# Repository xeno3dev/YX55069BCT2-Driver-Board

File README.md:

# LumaDD

## Overview

LumaDD is a Custom Display Driver Board designed around a display I got off [Alibaba](https://www.alibaba.com/product-detail/5-5-Vertical-Smart-Home-lcd_1601790231031.html?spm=a2756.trade-list-buyer.0.0.36a276e9iccSGK), with Touch Support. It features HDMI -> MIPI DSI video signal conversion, USB-C for Touch Signals + Power, as well as an onboard ESP32-S3 for display control + touch processing (via USB HID)

## Repo Directory

Folder | Contents
|---|---|
Component Libs | All 3D Models. Footprints, and Symbols used on the PCB
Kicad Project | Schematic + PCB Files
Production Files | BOM + CPL + Netlist + Designator + Gerber Files

## Rough BOM
| Part / Group | What’s included | Qty | Cost (USD) |
| --- | --- | ---: | ---: |
| Converter BGA | [TC358870XBG](https://www.lcsc.com/product-detail/C3008712.html), U1 | 1 | $8.86 |
| ESP32 by itself | [ESP32-S3R8](https://www.lcsc.com/product-detail/C2913194.html), U10 | 1 | $3.02 |
| Flash memory | [GD25Q128EWIGR](https://www.lcsc.com/product-detail/C2982923.html), U11 | 1 | $3.33 |
| HDMI port | [Amphenol 10029449-111RLF](https://www.lcsc.com/product-detail/C427307.html) | 1 | $0.62 |
| USB-C port | [TYPE-C16PIN](https://www.lcsc.com/product-detail/C393939.html) | 1 | $0.06 |
| Display connector | [24-pin FPC](https://www.lcsc.com/product-detail/C132514.html) | 1 | $0.25 |
| Touch connector | [6-pin FPC](https://www.lcsc.com/product-detail/C5343255.html) | 1 | $0.15 |
| Power regulation and input control | Five TLV767 regulators, CH224K, TPS259474 eFuse | 7 | $3.64 |
| Backlight power stage | TPS61165, inductor, diode | 3 | $1.09 |
| Logic level shifters | Two PCA9306, TXS0101, SN74AXC1T45 | 4 | $2.39 |
| ESD / surge protection | D3–D5, U8, U12, U16 | 6 | $1.46 |
| Clock components | 40 MHz crystal and 48 MHz oscillator | 2 | $1.50 |
| Boot / reset buttons | SW3 and SW4 | 2 | $2.29 |
| Capacitors | All BOM capacitors | 72 | $1.97 |
| Resistors | All BOM resistors | 40 | $0.36 |
| MOSFETs | Three BSS138 | 3 | $0.06 |
| Ferrite beads | FB1 and FB2 | 2 | $0.03 |
| **Total parts used** | **148 components** | **148** | **$31.07** |

### Full BOM Located [Here](./Production%20Files/bom.csv)

## License

[Attribution-NonCommercial-ShareAlike 4.0 International](./LICENSE)

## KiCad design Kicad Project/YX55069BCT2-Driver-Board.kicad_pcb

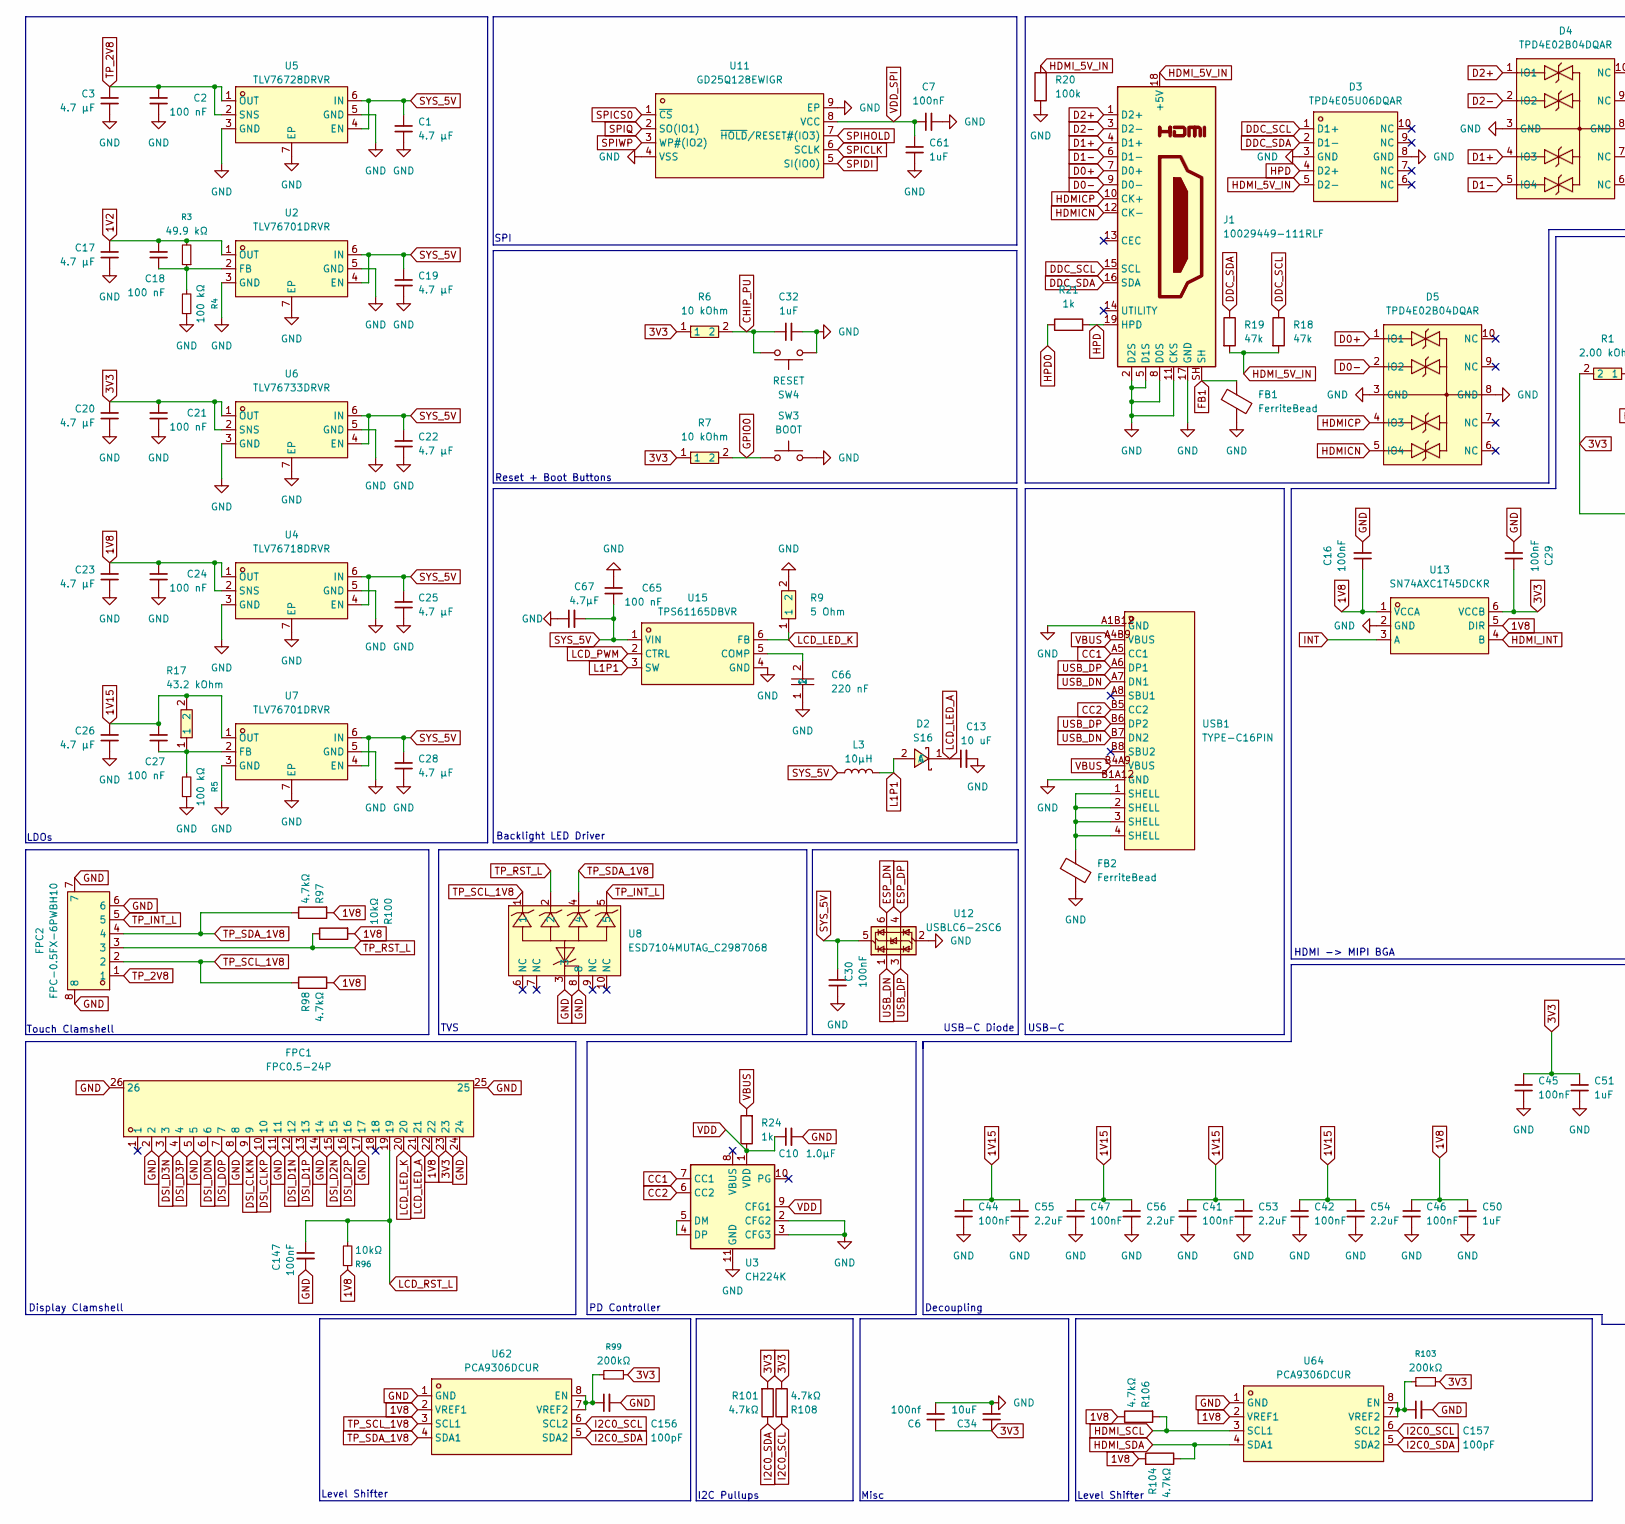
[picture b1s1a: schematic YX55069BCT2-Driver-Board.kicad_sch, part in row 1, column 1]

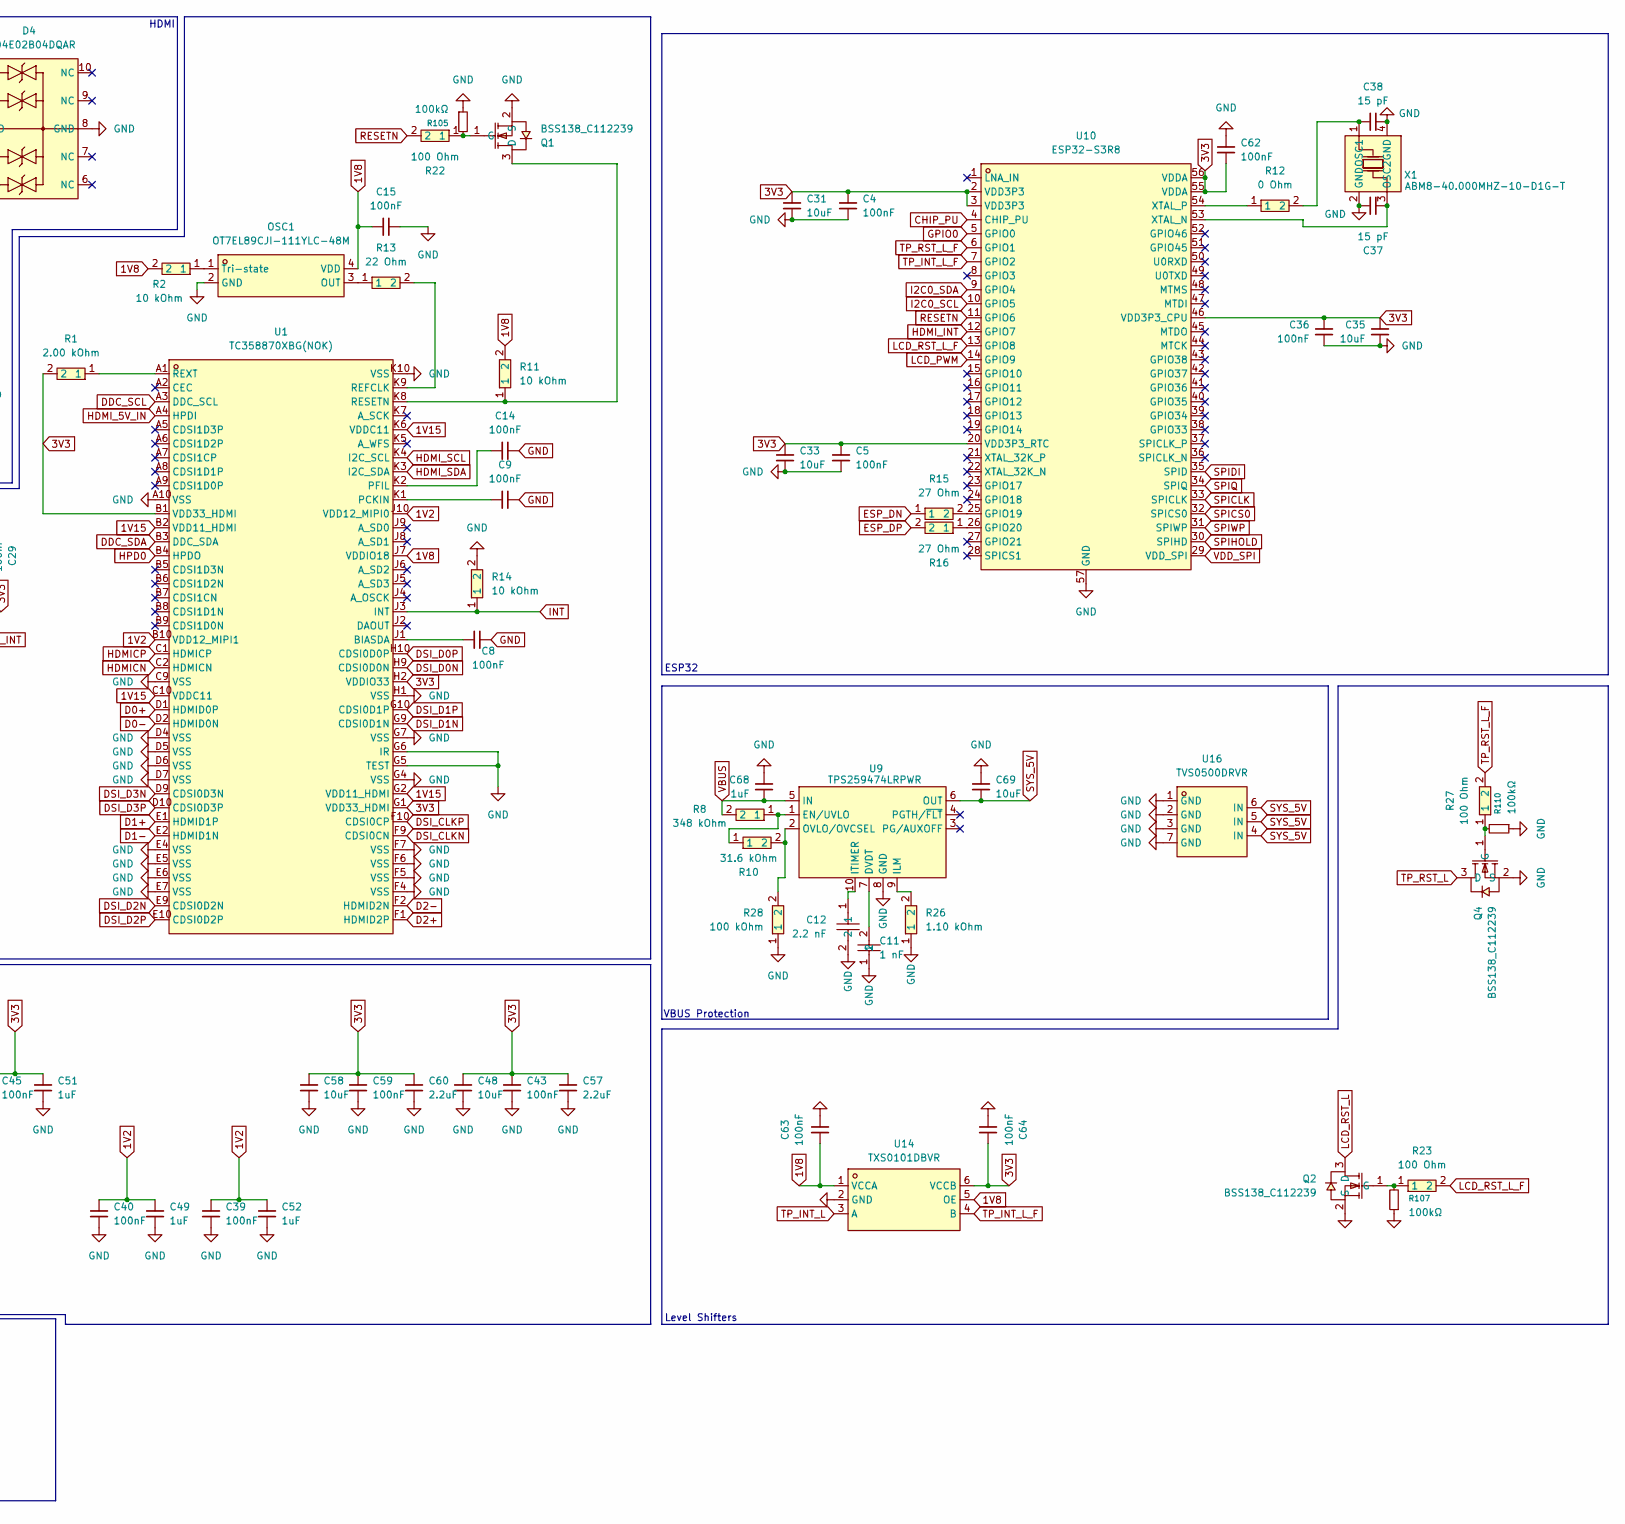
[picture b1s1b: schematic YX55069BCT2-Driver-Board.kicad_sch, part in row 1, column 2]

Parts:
C1, C3, C17, C19, C20, C22, C23, C25, C26, C28: 4.7 µF; C_0603_1608Metric; LCSC C69335
C2, C18, C21, C24, C27, C65: 100 nF; C_0603_1608Metric; LCSC C1591
C4, C5, C7, C8, C9, C14, C15, C16, C29, C30, C36, C39, C40, C41, C42, C43, C44, C45, C46, C47, C59, C62, C63, C64: 100nF; C0603; LCSC C1591
C6: 100nf; C0603; LCSC C1591
C10: 1.0µF; C_0603_1608Metric; MPN CL10A105KA8NNNC; LCSC Part C5673
C11: 1 nF; C0402; Tolerance 10%; Voltage 50 V; MPN CL05B102KB5NNNC; LCSC C14442
C12: 2.2 nF; C0402; Tolerance 10%; Voltage 50 V; MPN CL05B222KB5NNNC; LCSC C84703
C13: 10 uF; C1206; LCSC Part C100122
C31, C33, C34, C35, C48, C58, C69: 10uF; C0603; LCSC C77044
C32, C68: 1uF; CL05A105KA5NQNC; LCSC C52923
C37, C38: 15 pF; C0402; LCSC C86285
C49, C50, C51, C52, C61: 1uF; C0603; LCSC C29936
C53, C54, C55, C56, C57, C60: 2.2uF; C0603; LCSC C23630
C66: 220 nF; C0402; Tolerance 10%; Voltage 16 V; MPN CL05B224KO5NNNC; LCSC C16772
C67: 4.7µF; C0805; LCSC Part C2897302
C147: 100nF; C_0603_1608Metric; MPN CL10B104KB8NNNC; LCSC Part C1591
C156, C157: 100pF; C_0603_1608Metric; MPN CL10C101JB8NNNC; LCSC Part C14858
D2: S16; SOD-123FL_L2.7-W1.8-LS3.8-RD; MPN S16; LCSC C405304
D3: TPD4E05U06DQAR; USON-10_L2.5-W1.0-P0.50-BL; MPN TPD4E05U06DQAR; LCSC C138714
D4, D5: TPD4E02B04DQAR; USON-10_L2.5-W1.0-P0.50-BL; MPN TPD4E02B04DQAR; LCSC C106794
FB1, FB2: FerriteBead; L_0603_1608Metric; LCSC C14709
FPC1: FPC0.5-24P; FPC-SMD_P0.50-24P_XJ-FGS; MPN F-FPC0M24P-C310; LCSC Part C132514
FPC2: FPC-0.5FX-6PWBH10; FPC-SMD_FPC-0.5FX-6PWBH10; MPN FPC-0.5FX-6PWBH10; LCSC Part C5343255
J1: 10029449-111RLF; HDMI_A_Amphenol_10029449-x01xLF_Horizontal; MPN 10029449-001RLF; LCSC C427307
L3: 10µH; IND-SMD_L7.1-W6.6; MPN SPM6530T-100M; LCSC Part C112288
OSC1: OT7EL89CJI-111YLC-48M; OSC-SMD_4P-L2.0-W1.6-BL; Supply Voltage 1.8–3.3 V; MPN OT7EL89CJI-111YLC-48M; LCSC C7434946
Q1, Q2, Q4: BSS138_C112239; SOT-23-3_L2.9-W1.6-P1.90-LS2.8-BR; MPN BSS138; LCSC C112239
R1: 2.00 kOhm; R0402; Tolerance 1%; MPN RC0402FR-072KL; LCSC C60488
R2, R6, R7, R11, R14: 10 kOhm; R0402; Tolerance 1%; MPN RC0402FR-0710KL; LCSC C60490
R3: 49.9 kΩ; R_0805_2012Metric; LCSC C17719
R4, R5: 100 kΩ; R_0805_2012Metric; LCSC C149504
R8: 348 kOhm; R0402; Voltage 50 V; Tolerance 1%; MPN 0402WGF3483TCE; LCSC C25780
R9: 5 Ohm; R0402; Voltage 50 V; Tolerance 1%; MPN CSRT0402FT5R00; LCSC C6888654
R10: 31.6 kOhm; R0402; Voltage 50 V; Tolerance 1%; MPN 0402WGF3162TCE; LCSC C11463
R12: 0 Ohm; R0402; Tolerance 1%; MPN RC0402FR-070RL; LCSC C106231
R13: 22 Ohm; R0402; Tolerance 1%; MPN RC0402FR-0722RL; LCSC C114765
R15, R16: 27 Ohm; R0402; Tolerance 1%; MPN RC0402FR-0727RL; LCSC C138021
R17: 43.2 kOhm; R0402; Voltage 50 V; Tolerance 1%; MPN 0402WGF4322TCE; LCSC C25894
R18, R19: 47k; R_0603_1608Metric; LCSC C2907042
R20: 100k; R_0603_1608Metric; LCSC C14675
R21, R24: 1k; R_0603_1608Metric; LCSC C22548
R22, R23, R27: 100 Ohm; R0402; Tolerance 1%; MPN RC0402FR-07100RL; LCSC C106232
R26: 1.10 kOhm; R0402; Voltage 50 V; Tolerance 1%; MPN 0402WGF1101TCE; LCSC C25860
R28: 100 kOhm; R0402; Voltage 50 V; Tolerance 1%; MPN 0402WGF1003TCE; LCSC C25741
R96, R100: 10kΩ; R_0603_1608Metric; MPN CR0603-FX-1002ELF; LCSC Part C840630
R97, R98, R101, R104, R106, R108: 4.7kΩ; R_0603_1608Metric; MPN WR06X4701FTL; LCSC Part C163914
R99, R103: 200kΩ; R_0603_1608Metric; MPN ERJ3EKF2003V; LCSC Part C118142
R105, R107, R110: 100kΩ; R_0603_1608Metric; MPN 0603WAF1003T5E; LCSC Part C25803
SW3: BOOT; KEY-SMD_KMR2XXGXXX; MPN KMR231GLFS; LCSC Part C99271
SW4: RESET; KEY-SMD_KMR2XXGXXX; MPN KMR231GLFS; LCSC Part C99271
U1: TC358870XBG(NOK); P-VFBGA-80_L7.0-W7.0-R10-C10-P0.65-TL; MPN TC358870XBG(NOK); LCSC C3008712
U2, U7: TLV76701DRVR; WSON-6_L2.0-W2.0-P0.65-TL-EP; Output Voltage 1.0 V; MPN TLV76701DRVR; LCSC C2863998
U3: CH224K; SSOP-10-1EP_3.9x4.9mm_P1mm_EP2.1x3.3mm; MPN CH224K; LCSC Part C970725
U4: TLV76718DRVR; WSON-6_L2.0-W2.0-P0.65-BL-EP; Output Voltage 1.8 V; MPN TLV76718DRVR; LCSC C2870458
U5: TLV76728DRVR; WSON-6_L2.0-W2.0-P0.65-BL-EP; Output Voltage 2.8 V; MPN TLV76728DRVR; LCSC C2865665
U6: TLV76733DRVR; WSON-6_L2.0-W2.0-P0.65-TL-EP; Output Voltage 3.3 V; MPN TLV76733DRVR; LCSC C2848334
U8: ESD7104MUTAG_C2987068; DFN-10_L2.5-W1.0-P0.50-BL; MPN ESD7104MUTAG; LCSC Part C2987068
U9: TPS259474LRPWR; VQFN-10_L2.0-W2.0-P0.45-TL; MPN TPS259474LRPWR; LCSC C2864845
U10: ESP32-S3R8; QFN-56_L7.0-W7.0-P0.40-TL-EP4.0; MPN ESP32-S3R8; LCSC C2913194
U11: GD25Q128EWIGR; WSON-8_L6.0-W5.0-P1.27-TL-EP; MPN GD25Q128EWIGR; LCSC C2982923
U12: USBLC6-2SC6; SOT-23-6; LCSC C7519
U13: SN74AXC1T45DCKR; SC-70-6_L2.0-W1.3-P0.65-LS2.1-BL-1; MPN SN74AXC1T45DCKR; LCSC Part C2677392
U14: TXS0101DBVR; SOT-23-6_L2.9-W1.6-P0.95-LS2.8-BR; MPN TXS0101DBVR; LCSC C132604
U15: TPS61165DBVR; SOT-23-6_L2.9-W1.6-P0.95-LS2.8-BR; MPN TPS61165DBVR; LCSC C58756
U16: TVS0500DRVR; WSON-6_L2.0-W2.0-P0.65-BL-EP; MPN TVS0500DRVR; LCSC C609571
U62, U64: PCA9306DCUR; SSOP-8_L2.0-W2.3-P0.50-LS3.1-BR; MPN PCA9306DCUR; LCSC Part C33196
USB1: TYPE-C16PIN; USB-C-SMD_TYPE-C16PIN; MPN TYPE-C16PIN; LCSC C393939
X1: ABM8-40.000MHZ-10-D1G-T; CRYSTAL-SMD_4P-L3.2-W2.5-BL; MPN ABM8-40.000MHZ-10-D1G-T; LCSC C1986736

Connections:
1V2: C17.2, C18.2, C39.2, C40.2, C49.2, C52.2, R3.2, U1.B10 (VDD12_MIPI1), U1.J10 (VDD12_MIPI0), U2.1 (OUT)
1V8: C15.2, C16.2, C23.2, C24.2, C46.2, C50.2, C63.2, FPC1.22, OSC1.4 (VDD), R2.2, R11.2, R96.1, R97.2, R98.1, R100.2, R104.2, R106.1, U1.J7 (VDDIO18), U4.1 (OUT), U4.2 (SNS), U13.1 (VCCA), U13.5 (DIR), U14.1 (VCCA), U14.5 (OE), U62.2 (VREF1), U64.2 (VREF1)
1V15: C26.2, C27.2, C41.2, C42.2, C44.2, C47.2, C53.2, C54.2, C55.2, C56.2, R17.2, U1.B2 (VDD11_HDMI), U1.C10 (VDDC11), U1.G2 (VDD11_HDMI), U1.K6 (VDDC11), U7.1 (OUT)
3V3: C4.2, C5.2, C6.2, C20.2, C21.2, C29.2, C31.2, C33.2, C34.2, C35.2, C36.2, C43.2, C45.2, C48.2, C51.2, C57.2, C58.2, C59.2, C60.2, C62.2, C64.2, FPC1.23, R1.2, R6.1, R7.1, R99.2, R101.2, R103.2, R108.1, U1.B1 (VDD33_HDMI), U1.G1 (VDD33_HDMI), U1.H2 (VDDIO33), U6.1 (OUT), U6.2 (SNS), U10.2 (VDD3P3), U10.3 (VDD3P3), U10.20 (VDD3P3_RTC), U10.46 (VDD3P3_CPU), U10.55 (VDDA), U10.56 (VDDA), U13.6 (VCCB), U14.6 (VCCB)
CC1: U3.7 (CC1), USB1.A5 (CC1)
CC2: U3.6 (CC2), USB1.B5 (CC2)
CHIP_PU: C32.2, R6.2, SW4.1, U10.4 (CHIP_PU)
D0+: D5.1 (IO1), J1.7 (D0+), U1.D1 (HDMID0P)
D0-: D5.2 (IO2), J1.9 (D0-), U1.D2 (HDMID0N)
D1+: D4.4 (IO3), J1.4 (D1+), U1.E1 (HDMID1P)
D1-: D4.5 (IO4), J1.6 (D1-), U1.E2 (HDMID1N)
D2+: D4.1 (IO1), J1.1 (D2+), U1.F1 (HDMID2P)
D2-: D4.2 (IO2), J1.3 (D2-), U1.F2 (HDMID2N)
DDC_SCL: D3.1 (D1+), J1.15 (SCL), R18.1, U1.A3 (DDC_SCL)
DDC_SDA: D3.2 (D1-), J1.16 (SDA), R19.1, U1.B3 (DDC_SDA)
DSI_CLKN: FPC1.9, U1.F9 (CDSI0CN)
DSI_CLKP: FPC1.10, U1.F10 (CDSI0CP)
DSI_D0N: FPC1.6, U1.H9 (CDSI0D0N)
DSI_D0P: FPC1.7, U1.H10 (CDSI0D0P)
DSI_D1N: FPC1.12, U1.G9 (CDSI0D1N)
DSI_D1P: FPC1.13, U1.G10 (CDSI0D1P)
DSI_D2N: FPC1.15, U1.E9 (CDSI0D2N)
DSI_D2P: FPC1.16, U1.E10 (CDSI0D2P)
DSI_D3N: FPC1.3, U1.D9 (CDSI0D3N)
DSI_D3P: FPC1.4, U1.D10 (CDSI0D3P)
ESP_DN: R15.1, U12.6 (I/O1)
ESP_DP: R16.2, U12.4 (I/O2)
FB1: FB1.1, J1.SH
GND: C1.2, C2.1, C3.1, C4.1, C5.1, C6.1, C7.1, C8.1, C9.1, C10.2, C11.1, C12.2, C13.2, C14.1, C15.1, C16.1, C17.1, C19.2, C20.1, C21.1, C22.2, C23.1, C24.1, C25.2, C26.1, C28.2, C29.1, C30.2, C31.1, C32.1, C33.1, C34.1, C35.1, C36.1, C37.1, C38.1, C39.1, C40.1, C41.1, C42.1, C43.1, C44.1, C45.1, C46.1, C47.1, C48.1, C49.1, C50.1, C51.1, C52.1, C53.1, C54.1, C55.1, C56.1, C57.1, C58.1, C59.1, C60.1, C61.1, C62.1, C63.1, C64.1, C65.2, C66.1, C67.1, C68.1, C69.2, C147.2, C156.2, C157.2, D3.3 (GND), D3.8 (GND), D4.3 (GND), D4.8 (GND), D5.3 (GND), D5.8 (GND), FB1.2, FB2.2, FPC1.2, FPC1.5, FPC1.8, FPC1.11, FPC1.14, FPC1.17, FPC1.24, FPC1.25, FPC1.26, FPC2.6, FPC2.7, FPC2.8, J1.2 (D2S), J1.5 (D1S), J1.8 (D0S), J1.11 (CKS), J1.17 (GND), OSC1.2 (GND), Q1.2 (S), Q2.2 (S), Q4.2 (S), R4.1, R5.1, R9.2, R14.2, R20.2, R26.1, R28.1, R105.1, R107.1, R110.1, SW3.2, SW4.2, U1.A10 (VSS), U1.C9 (VSS), U1.D4 (VSS), U1.D5 (VSS), U1.D6 (VSS), U1.D7 (VSS), U1.E4 (VSS), U1.E5 (VSS), U1.E6 (VSS), U1.E7 (VSS), U1.F4 (VSS), U1.F5 (VSS), U1.F6 (VSS), U1.F7 (VSS), U1.G4 (VSS), U1.G5 (TEST), U1.G6 (IR), U1.G7 (VSS), U1.H1 (VSS), U1.K10 (VSS), U2.3 (GND), U2.5 (GND), U2.7 (EP), U3.2 (CFG2), U3.3 (CFG3), U3.11 (GND), U4.3 (GND), U4.5 (GND), U4.7 (EP), U5.3 (GND), U5.5 (GND), U5.7 (EP), U6.3 (GND), U6.5 (GND), U6.7 (EP), U7.3 (GND), U7.5 (GND), U7.7 (EP), U8.3, U8.8, U9.8 (GND), U10.57 (GND), U11.4 (VSS), U11.9 (EP), U12.2 (GND), U13.2 (GND), U14.2 (GND), U15.4 (GND), U16.1 (GND), U16.2 (GND), U16.3 (GND), U16.7 (GND), U62.1 (GND), U64.1 (GND), USB1.A1B12 (GND), USB1.B1A12 (GND), X1.2 (GND), X1.4 (GND)
GPIO0: R7.2, SW3.1, U10.5 (GPIO0)
HDMICN: D5.5 (IO4), J1.12 (CK-), U1.C2 (HDMICN)
HDMICP: D5.4 (IO3), J1.10 (CK+), U1.C1 (HDMICP)
HDMI_5V_IN: D3.5 (D2-), J1.18 (+5V), R18.2, R19.2, R20.1, U1.A4 (HPDI)
HDMI_INT: U10.12 (GPIO7), U13.4 (B)
HDMI_SCL: R106.2, U1.K4 (I2C_SCL), U64.3 (SCL1)
HDMI_SDA: R104.1, U1.K3 (I2C_SDA), U64.4 (SDA1)
HPD: D3.4 (D2+), J1.19 (HPD), R21.2
HPD0: R21.1, U1.B4 (HPDO)
I2C0_SCL: R108.2, U10.10 (GPIO5), U62.6 (SCL2), U64.6 (SCL2)
I2C0_SDA: R101.1, U10.9 (GPIO4), U62.5 (SDA2), U64.5 (SDA2)
INT: R14.1, U1.J3 (INT), U13.3 (A)
L1P1: D2.2 (A), L3.2, U15.3 (SW)
LCD_LED_A: C13.1, D2.1 (C), FPC1.21
LCD_LED_K: FPC1.20, R9.1, U15.6 (FB)
LCD_PWM: U10.14 (GPIO9), U15.2 (CTRL)
LCD_RST_L: C147.1, FPC1.19, Q2.3 (D), R96.2
LCD_RST_L_F: R23.2, U10.13 (GPIO8)
unnamed: FB2.1, USB1.1 (SHELL), USB1.2 (SHELL), USB1.3 (SHELL), USB1.4 (SHELL)
unnamed: OSC1.3 (OUT), R13.1
unnamed: OSC1.1 (Tri-state), R2.1
unnamed: Q1.3 (D), R11.1, U1.K8 (RESETN)
unnamed: Q1.1 (G), R22.1, R105.2
unnamed: Q2.1 (G), R23.1, R107.2
unnamed: Q4.1 (G), R27.1, R110.2
unnamed: C8.2, U1.J1 (BIASDA)
unnamed: C9.2, U1.K1 (PCKIN)
unnamed: C14.2, U1.K2 (PFIL)
unnamed: R13.2, U1.K9 (REFCLK)
unnamed: R1.1, U1.A1 (REXT)
unnamed: C18.1, R3.1, R4.2, U2.2 (FB)
unnamed: U3.4 (DP), U3.5 (DM)
unnamed: C27.1, R5.2, R17.1, U7.2 (FB)
unnamed: C11.2, U9.7 (DVDT)
unnamed: R8.1, R10.1, U9.1 (EN/UVLO)
unnamed: R26.2, U9.9 (ILM)
unnamed: C12.1, U9.10 (ITIMER)
unnamed: R10.2, R28.2, U9.2 (OVLO/OVCSEL)
unnamed: R15.2, U10.25 (GPIO19)
unnamed: R16.1, U10.26 (GPIO20)
unnamed: C37.2, U10.53 (XTAL_N), X1.3 (OSC2)
unnamed: R12.1, U10.54 (XTAL_P)
unnamed: C66.2, U15.5 (COMP)
unnamed: C156.1, R99.1, U62.7 (VREF2), U62.8 (EN)
unnamed: C157.1, R103.1, U64.7 (VREF2), U64.8 (EN)
unnamed: C38.2, R12.2, X1.1 (OSC1)
RESETN: R22.2, U10.11 (GPIO6)
SPICLK: U10.33 (SPICLK), U11.6 (SCLK)
SPICS0: U10.32 (SPICS0), U11.1 (~CS)
SPIDI: U10.35 (SPID), U11.5 (SI(IO0))
SPIHOLD: U10.30 (SPIHD), U11.7 (~HOLD/RESET#(IO3))
SPIQ: U10.34 (SPIQ), U11.2 (SO(IO1))
SPIWP: U10.31 (SPIWP), U11.3 (WP#(IO2))
SYS_5V: C1.1, C19.1, C22.1, C25.1, C28.1, C30.1, C65.1, C67.2, C69.1, L3.1, U2.4 (EN), U2.6 (IN), U4.4 (EN), U4.6 (IN), U5.4 (EN), U5.6 (IN), U6.4 (EN), U6.6 (IN), U7.4 (EN), U7.6 (IN), U9.6 (OUT), U12.5 (VBUS), U15.1 (VIN), U16.4 (IN), U16.5 (IN), U16.6 (IN)
TP_2V8: C2.2, C3.2, FPC2.1, U5.1 (OUT), U5.2 (SNS)
TP_INT_L: FPC2.5, U8.5, U14.3 (A)
TP_INT_L_F: U10.7 (GPIO2), U14.4 (B)
TP_RST_L: FPC2.3, Q4.3 (D), R100.1, U8.2
TP_RST_L_F: R27.2, U10.6 (GPIO1)
TP_SCL_1V8: FPC2.2, R98.2, U8.1, U62.3 (SCL1)
TP_SDA_1V8: FPC2.4, R97.1, U8.4, U62.4 (SDA1)
USB_DN: U12.1 (I/O1), USB1.A7 (DN1), USB1.B7 (DN2)
USB_DP: U12.3 (I/O2), USB1.A6 (DP1), USB1.B6 (DP2)
VBUS: C68.2, R8.2, R24.2, U9.5 (IN), USB1.A4B9 (VBUS), USB1.B4A9 (VBUS)
VDD: C10.1, R24.1, U3.1 (VDD), U3.9 (CFG1)
VDD_SPI: C7.2, C61.2, U10.29 (VDD_SPI), U11.8 (VCC)

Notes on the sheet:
Reset + Boot Buttons
Misc
I2C Pullups
Level Shifter
SPI
USB-C Diode
HDMI
TVS
Touch Clamshell
ESP32
Backlight LED Driver
Decoupling
VBUS Protection
USB-C
PD Controller
HDMI -> MIPI BGA
LDOs
Level Shifters
Display Clamshell

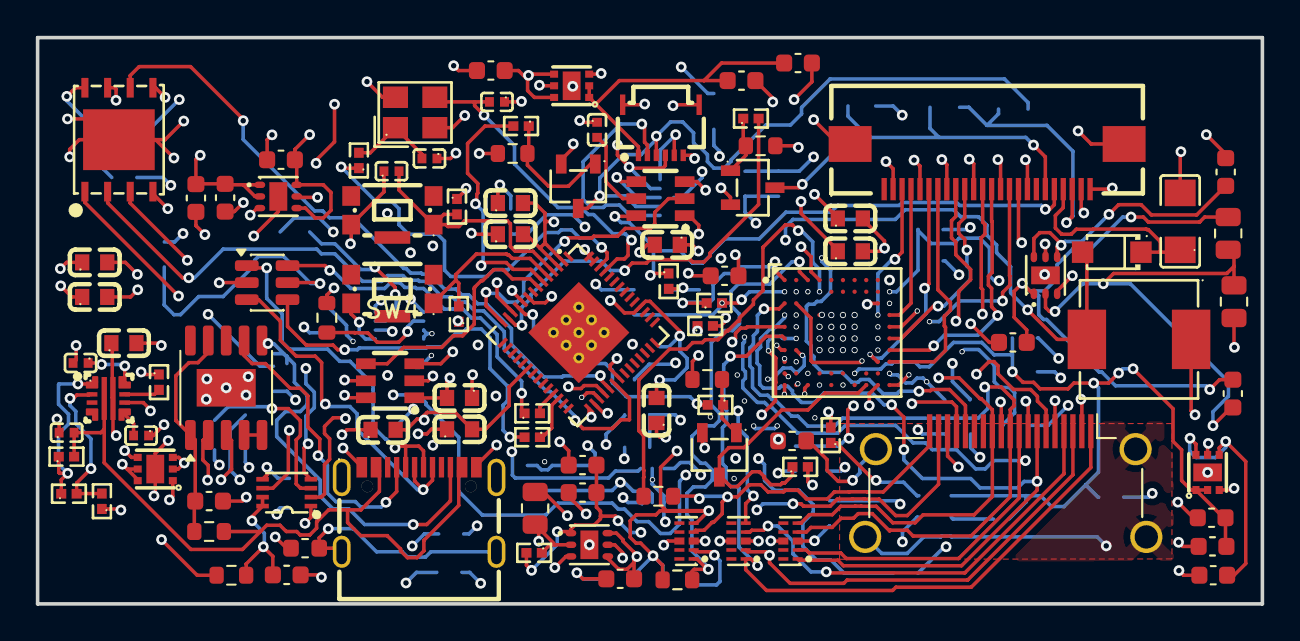
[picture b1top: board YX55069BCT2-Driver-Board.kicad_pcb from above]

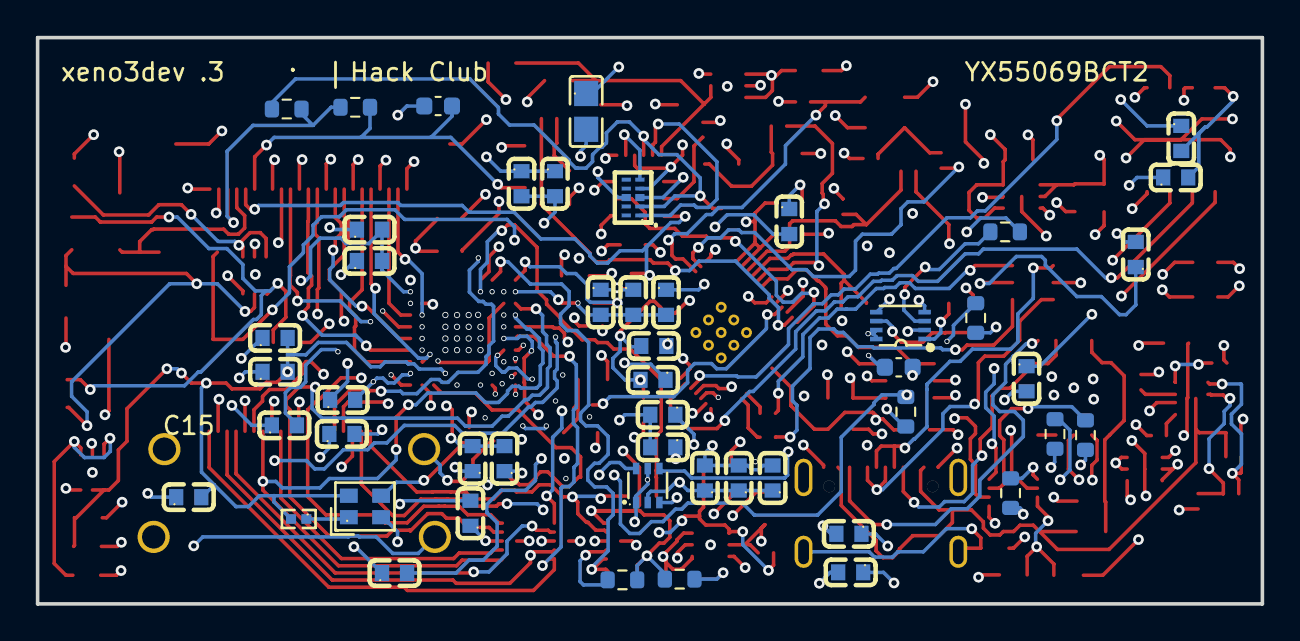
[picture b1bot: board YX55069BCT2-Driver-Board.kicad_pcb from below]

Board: 8 copper layers, 68.4 x 31.6 mm, 148 parts (49 on the bottom side), 95 nets.

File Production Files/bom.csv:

Designator,Footprint,Quantity,Value,LCSC Part #
"C1, C17, C19, C20, C22, C23, C25, C26, C28, C3",0603,10,4.7 µF,C69335
C10,0603,1,1.0µF,C5673
C11,C0402,1,1 nF,C14442
C12,C0402,1,2.2 nF,C84703
C13,C1206,1,10 uF,C100122
"C14, C15, C16, C29, C30, C36, C39, C4, C40, C41, C42, C43, C44, C45, C46, C47, C5, C59, C6, C62, C63, C64, C7, C8, C9",C0603,25,100nF,C1591
C147,0603,1,100nF,C1591
"C156, C157",0603,2,100pF,C14858
"C18, C2, C21, C24, C27, C65",0603,6,100 nF,C1591
"C31, C33, C34, C35, C48, C58, C69",C0603,7,10uF,C77044
"C32, C68",CL05A105KA5NQNC,2,1uF,C52923
"C37, C38",C0402,2,15 pF,C86285
"C49, C50, C51, C52, C61",C0603,5,1uF,C29936
"C53, C54, C55, C56, C57, C60",C0603,6,2.2uF,C23630
C66,C0402,1,220 nF,C16772
C67,C0805,1,4.7µF,C2897302
D2,SOD-123FL_L2.7-W1.8-LS3.8-RD,1,S16,C405304
D3,USON-10_L2.5-W1.0-P0.50-BL,1,TPD4E05U06DQAR,C138714
"D4, D5",USON-10_L2.5-W1.0-P0.50-BL,2,TPD4E02B04DQAR,C106794
"FB1, FB2",0603,2,FerriteBead,C14709
FPC1,FPC-SMD_P0.50-24P_XJ-FGS,1,FPC0.5-24P,C132514
FPC2,FPC-SMD_FPC-0.5FX-6PWBH10,1,FPC-0.5FX-6PWBH10,C5343255
J1,HDMI_A_Amphenol_10029449-x01xLF_Horizontal,1,10029449-111RLF,C427307
L3,IND-SMD_L7.1-W6.6,1,10µH,C112288
OSC1,OSC-SMD_4P-L2.0-W1.6-BL,1,OT7EL89CJI-111YLC-48M,C7434946
"Q1, Q2, Q4",SOT-23-3_L2.9-W1.6-P1.90-LS2.8-BR,3,BSS138_C112239,C112239
R1,R0402,1,2.00 kOhm,C60488
R10,R0402,1,31.6 kOhm,C11463
"R100, R96",0603,2,10kΩ,C840630
"R101, R104, R106, R108, R97, R98",0603,6,4.7kΩ,C163914
"R103, R99",0603,2,200kΩ,C118142
"R105, R107, R110",0603,3,100kΩ,C25803
"R11, R14, R2, R6, R7",R0402,5,10 kOhm,C60490
R12,R0402,1,0 Ohm,C106231
R13,R0402,1,22 Ohm,C114765
"R15, R16",R0402,2,27 Ohm,C138021
R17,R0402,1,43.2 kOhm,C25894
"R18, R19",0603,2,47k,C2907042
R20,0603,1,100k,C14675
"R21, R24",0603,2,1k,C22548
"R22, R23, R27",R0402,3,100 Ohm,C106232
R26,R0402,1,1.10 kOhm,C25860
R28,R0402,1,100 kOhm,C25741
R3,0805,1,49.9 kΩ,C17719
"R4, R5",0805,2,100 kΩ,C149504
R8,R0402,1,348 kOhm,C25780
R9,R0402,1,5 Ohm,C6888654
SW3,KEY-SMD_KMR2XXGXXX,1,BOOT,C99271
SW4,KEY-SMD_KMR2XXGXXX,1,RESET,C99271
U1,P-VFBGA-80_L7.0-W7.0-R10-C10-P0.65-TL,1,TC358870XBG(NOK),C3008712
U10,QFN-56_L7.0-W7.0-P0.40-TL-EP4.0,1,ESP32-S3R8,C2913194
U11,WSON-8_L6.0-W5.0-P1.27-TL-EP,1,GD25Q128EWIGR,C2982923
U12,SOT-23-6,1,USBLC6-2SC6,C7519
U13,SC-70-6_L2.0-W1.3-P0.65-LS2.1-BL-1,1,SN74AXC1T45DCKR,C2677392
U14,SOT-23-6_L2.9-W1.6-P0.95-LS2.8-BR,1,TXS0101DBVR,C132604
U15,SOT-23-6_L2.9-W1.6-P0.95-LS2.8-BR,1,TPS61165DBVR,C58756
U16,WSON-6_L2.0-W2.0-P0.65-BL-EP,1,TVS0500DRVR,C609571
"U2, U7",WSON-6_L2.0-W2.0-P0.65-TL-EP,2,TLV76701DRVR,C2863998
U3,SSOP-10-1EP_3.9x4.9mm_P1mm_EP2.1x3.3mm,1,CH224K,C970725
U4,WSON-6_L2.0-W2.0-P0.65-BL-EP,1,TLV76718DRVR,C2870458
U5,WSON-6_L2.0-W2.0-P0.65-BL-EP,1,TLV76728DRVR,C2865665
U6,WSON-6_L2.0-W2.0-P0.65-TL-EP,1,TLV76733DRVR,C2848334
"U62, U64",SSOP-8_L2.0-W2.3-P0.50-LS3.1-BR,2,PCA9306DCUR,C33196
U8,DFN-10_L2.5-W1.0-P0.50-BL,1,ESD7104MUTAG_C2987068,C2987068
U9,VQFN-10_L2.0-W2.0-P0.45-TL,1,TPS259474LRPWR,C2864845
USB1,USB-C-SMD_TYPE-C16PIN,1,TYPE-C16PIN,C393939
X1,CRYSTAL-SMD_4P-L3.2-W2.5-BL,1,ABM8-40.000MHZ-10-D1G-T,C1986736

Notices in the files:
README.md:
License: CC BY-NC-SA 4.0
